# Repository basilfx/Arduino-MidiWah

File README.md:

# MidiWah v1.0
Arduino based bridge between a wah-wah (e.g. Dunlop GCB-95) and its potentiometer. Digitizes the potentiometer and feeds it via a digital potentiometer back to the circuit.

As a bonus, the digitized potentiometer signal can be  outputted via MIDI OUT.

## Contents
* Eagle schematic and PCB
* Arduino firmware

## Eagle

### Bill of materials
An Atmega328 can also be used. The R7-R9 are 0-ohm jumpers. The MCP4251 has a range of 0-100k.

| Part | Value     | Device          | Package           |
|------|-----------|-----------------|-------------------|
| C1   | 22pF      | C-EU025-024X044 | C025-024X044      |
| C2   | 22pF      | C-EU025-024X044 | C025-024X044      |
| C3   | 1µF       | CPOL-EUE2.5-5   | E2,5-5            |
| C4   | 1µF       | CPOL-EUE2.5-5   | E2,5-5            |
| C5   | 100nF     | C-EU025-024X044 | C025-024X044      |
| C6   | 100nF     | C-EU025-024X044 | C025-024X044      |
| C7   | 100nF     | C-EU025-024X044 | C025-024X044      |
| C8   | 100nF     | C-EU025-024X044 | C025-024X044      |
| D1   | 1N4148    | 1N4148          | DO35-7            |
| IC1  | ATMEGA168 | MEGA8-P         | DIL28-3           |
| IC2  | 7805L     | 7805L           | TO92              |
| IC3  | MCP4251   | MCP4251-104     | DIP254P762X533-14 |
| IC4  | 6N138     | 6N138           | DIL08             |
| Q1   | 16MHz     | CRYSTALHC49S    | HC49/S            |
| R1   | 10k       | R-EU_0204/7     | 0204/7            |
| R2   | 220       | R-EU_0204/7     | 0204/7            |
| R3   | 1k        | R-EU_0204/7     | 0204/7            |
| R4   | 220       | R-EU_0204/7     | 0204/7            |
| R5   | 1k        | R-EU_0204/7     | 0204/7            |
| R6   | 1k        | R-EU_0204/2V    | 0204V             |
| R7   | 0         | R-EU_M0805      | M0805             |
| R8   | 0         | R-EU_M0805      | M0805             |
| R9   | 0         | R-EU_M0805      | M0805             |
| SW1  |           | SW_DIP-4        | EDG-04            |

### Board render
The board measures 1.70x2.10 inch. Below a render of the top and bottom.

## Arduino
The source can be found under `firmware`. It's build with Arduino 1.0.5, but newer versions should work too.

See the `firmware/UsedLibraries.md` for the libraries to install.

### Firmware
To be done.

### Configuration
The DIP switch on the PCB select the channel to which the MidiWah will respond

The firmware can be programmed via a few MIDI Control Change messages. Changes are only persisted when a save command is issued.

* `CC 80 [0|1]` &mdash; disable or enable calibration of the potentiometer. Replies with the same value.
* `CC 81 [0|1]` &mdash; disable or enable invertion of the potentiometer value. Replies with the same value.
* `CC 82 [0-2]` &mdash; select potentiometer program. Replies with the selected program, or the last one if program is invalid.
  * Program 0 is linear
  * Program 1 is logarithmic
  * Program 3 is first 50% from 0 to 127 and the next 50% from 127 to 0
* `CC 83 [x]` &mdash; save settings to EEPROM. The parameter `x` can be anything. Responds with same message.

## License
See the `LICENSE` file (MIT license).

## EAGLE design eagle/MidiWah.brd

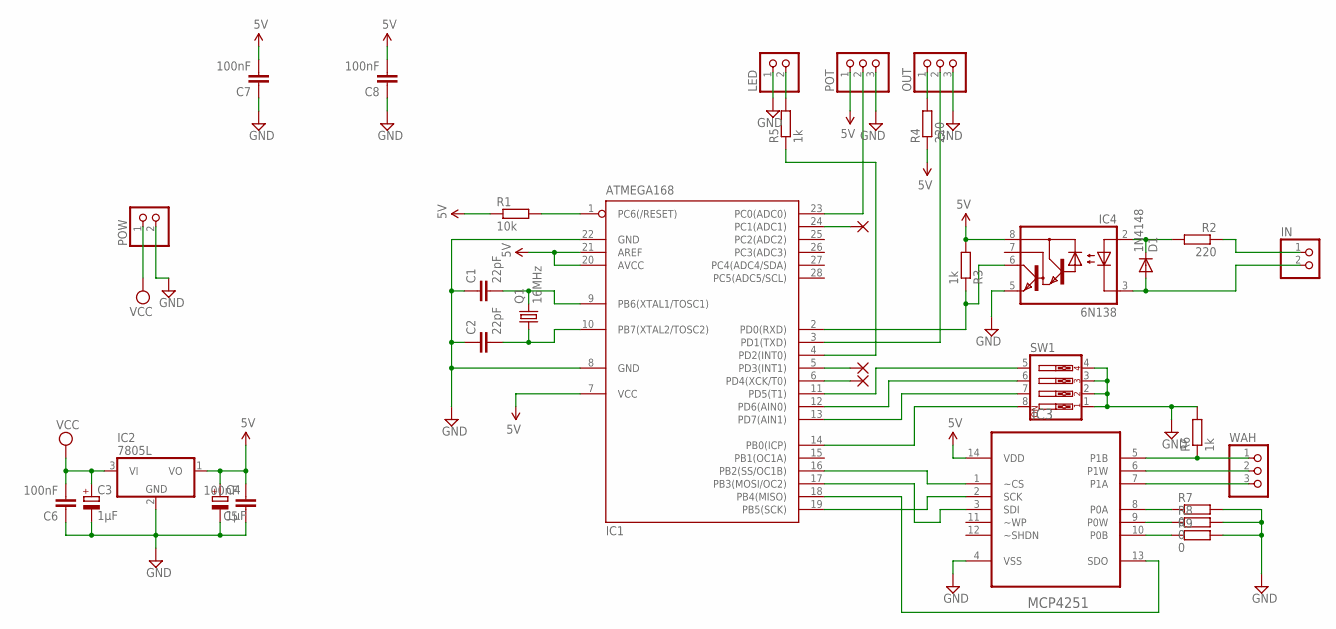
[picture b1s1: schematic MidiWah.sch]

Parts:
C1, C2: 22pF; C025-024X044
C3, C4: 1µF; E2,5-5
C5, C6, C7, C8: 100nF; C025-024X044
D1: 1N4148; DO35-7
IC1: ATMEGA168; DIL28-3
IC2: 7805L; TO92
IC3: MCP4251; DIP254P762X533-14
IC4: 6N138; DIL08
IN: PINHD-1X2; 1X02
LED: PINHD-1X2; 1X02
OUT: PINHD-1X3; 1X03
PAD1, PAD2, PAD3: WIREPAD1,6/0,8; 1,6/0,8
POT: PINHD-1X3; 1X03
POW: PINHD-1X2; 1X02
Q1: 16MHz; HC49/S
R1: 10k; 0204/7
R2, R4: 220; 0204/7
R3, R5: 1k; 0204/7
R6: 1k; 0204V
R7, R8, R9: 0; M0805
SW1: SW_DIP-4; EDG-04
WAH: PINHD-1X3; 1X03

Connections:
5V: C4.+, C5.2, C7.2, C8.2, IC1.7 (VCC), IC1.20 (AVCC), IC1.21 (AREF), IC2.1 (VO), IC3.14 (VDD), IC4.8 (VCC), POT.1, R1.1, R3.2, R4.1
GND: C1.1, C2.1, C3.-, C4.-, C5.1, C6.1, C7.1, C8.1, IC1.8 (GND), IC1.22 (GND), IC2.2 (GND), IC3.4 (VSS), IC4.5 (GND), LED.1, OUT.3, POT.3, POW.2, R6.2, R7.2, R8.2, R9.2, SW1.1, SW1.2, SW1.3, SW1.4
unnamed: IC1.1 (PC6(/RESET)), R1.2
unnamed: IC1.16 (PB2(SS/OC1B)), IC3.1 (~CS)
unnamed: C1.2, IC1.9 (PB6(XTAL1/TOSC1)), Q1.2
unnamed: C2.2, IC1.10 (PB7(XTAL2/TOSC2)), Q1.1
unnamed: IC1.19 (PB5(SCK)), IC3.2 (SCK)
unnamed: IC1.18 (PB4(MISO)), IC3.13 (SDO)
unnamed: IC1.17 (PB3(MOSI/OC2)), IC3.3 (SDI)
unnamed: D1.A, IC4.3 (C), IN.2
unnamed: D1.C, IC4.2 (A), R2.2
unnamed: IN.1, R2.1
unnamed: IC1.2 (PD0(RXD)), IC4.6 (VO), R3.1
unnamed: IC1.14 (PB0(ICP)), SW1.8
unnamed: IC1.13 (PD7(AIN1)), SW1.7
unnamed: IC1.12 (PD6(AIN0)), SW1.6
unnamed: IC1.11 (PD5(T1)), SW1.5
unnamed: IC1.23 (PC0(ADC0)), POT.2
unnamed: IC3.6 (P1W), WAH.2
unnamed: IC3.8 (P0A), R7.1
unnamed: IC3.7 (P1A), WAH.3
unnamed: IC1.3 (PD1(TXD)), OUT.2
unnamed: OUT.1, R4.2
unnamed: LED.2, R5.2
unnamed: IC1.4 (PD2(INT0)), R5.1
unnamed: IC3.5 (P1B), R6.1, WAH.1
unnamed: IC3.9 (P0W), R8.1
unnamed: IC3.10 (P0B), R9.1
unnamed: IC1.5 (PD3(INT1)), PAD2.1
unnamed: IC1.6 (PD4(XCK/T0)), PAD3.1
unnamed: IC1.24 (PC1(ADC1)), PAD1.1
VCC: C3.+, C6.2, IC2.3 (VI), POW.1

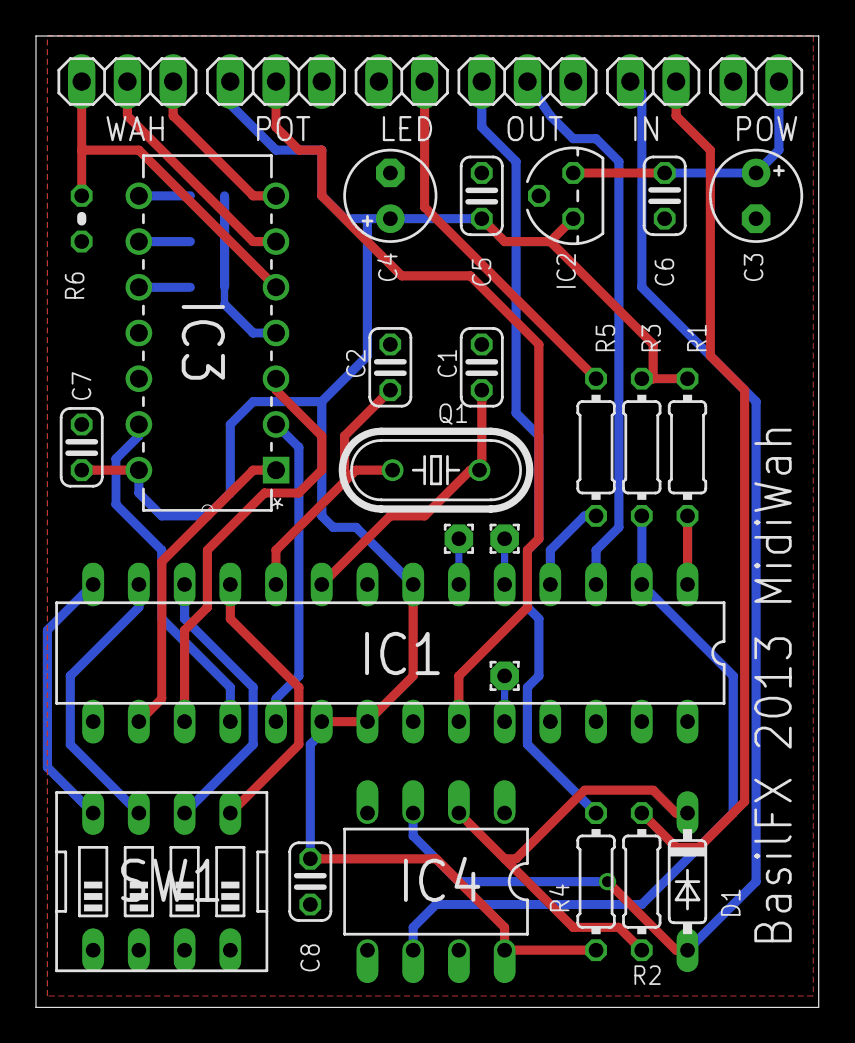
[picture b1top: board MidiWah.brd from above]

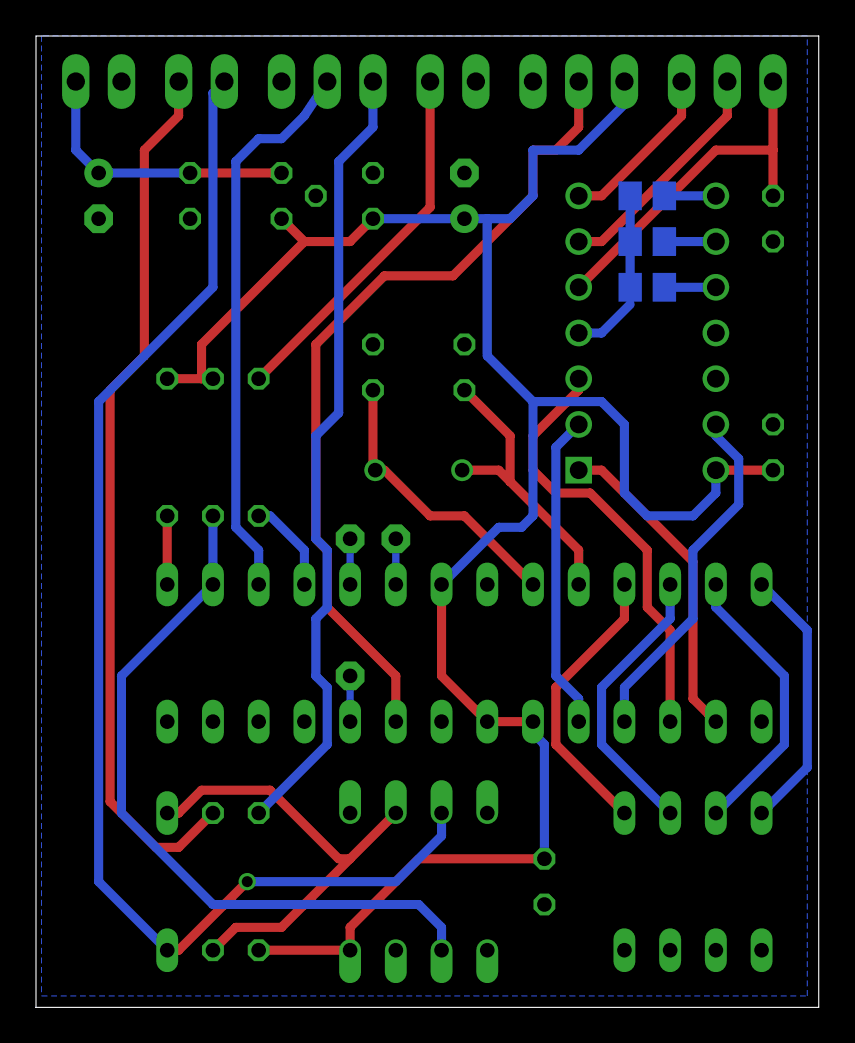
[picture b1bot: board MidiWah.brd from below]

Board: 2 copper layers, 43.5 x 54.0 mm, 33 parts (3 on the bottom side), 32 nets.

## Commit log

2014-12-20 Added board render and BOM

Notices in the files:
parts and their libraries:
SparkFun: Licensing: CC v3.0 Share-Alike You are welcome to use this library for commercial purposes.
